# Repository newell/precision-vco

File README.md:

# Precision Voltage-Controlled Oscillator (VCO)

This circuit is a precision voltage-controlled oscillator (VCO), where the frequency of oscillation is determined by a control voltage. It consists of an integrator and a Schmitt trigger.

### Integrator
The first op-amp in the circuit acts as an integrator. The control voltage is divided using a voltage divider and applied to the positive input of the op-amp. The op-amp strives to keep its negative input at the same voltage level. This requires a current to flow through a resistor to maintain a specific voltage drop.

When a switch, such as a MOSFET, is on, the current from the resistor passes through the switch. Another resistor, connected in parallel with the switch, has a different resistance but the same voltage drop. As a result, it carries a different amount of current. This additional current either charges or discharges a capacitor, depending on the state of the switch. The integrator adjusts its output voltage to accommodate this current flow, resulting in a steadily rising or falling output voltage.

### Schmitt Trigger
The second op-amp in the circuit functions as a Schmitt trigger. It receives the output from the integrator as its input. The Schmitt trigger compares the input voltage with two threshold levels. When the input voltage rises above the upper threshold, the output switches to a high state. Conversely, when the input voltage falls below the lower threshold, the output switches to a low state. This behavior generates a square wave output.

The square wave output from the Schmitt trigger is connected to the switch (e.g., MOSFET) in the circuit. The switch controls the charging and discharging of the capacitor in the integrator circuit. As the square wave switches between its high and low states, it causes the integrator to adjust its output voltage accordingly, resulting in the generation of a triangle wave.

<!-- # aoe-precision-vco
Art of Electronics (AOE) Precision VCO

This circuit is based off of an AOE (Art of Electronics, 3rd Edition) circuit example found on page 267 (Figure 4.83). This circuit outputs triangle and square waves with frequencies equal to 200 * Vin Hz where Vin is from 0 to 2*Vref. In this circuit Vref is 5 V so we have a frequency range of 0 to 2 kHz -->

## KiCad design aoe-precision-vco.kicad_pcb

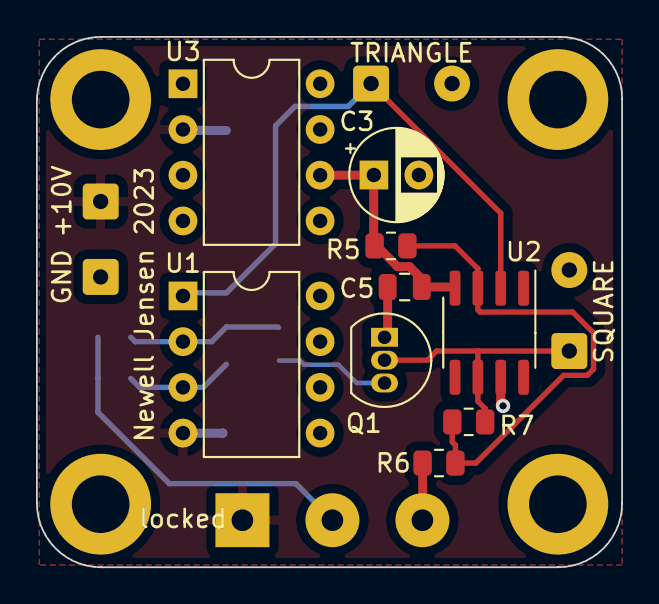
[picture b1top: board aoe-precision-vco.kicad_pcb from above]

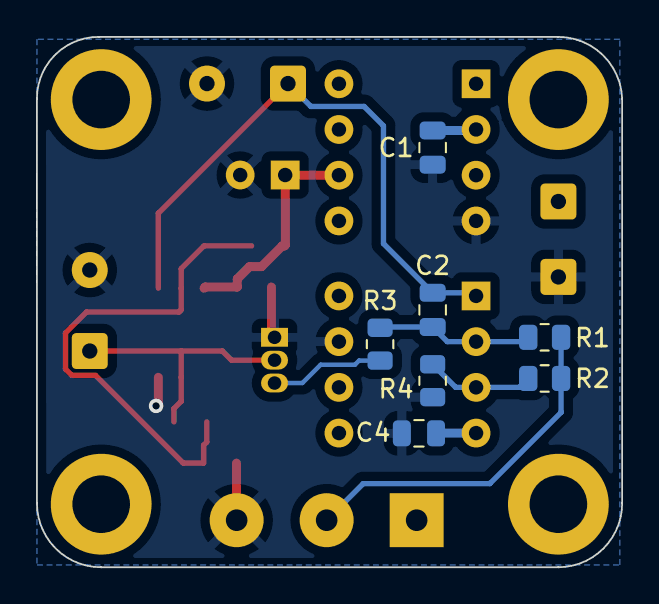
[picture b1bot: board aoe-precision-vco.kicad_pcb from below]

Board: 2 copper layers, 32.5 x 29.5 mm, 21 parts (7 on the bottom side), 10 nets.

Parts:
+10V: Conn_01x01; SolderWire-0.25sqmm_1x01_D0.65mm_OD2mm
C1, C2, C4, C5: 0.1uF; C_0805_2012Metric
C3: 4.7uF; CP_Radial_D5.0mm_P2.50mm
GND: Conn_01x01; SolderWire-0.25sqmm_1x01_D0.65mm_OD2mm
Q1: 2N7000; TO-92_Inline
R1: 7.5k; R_0805_2012Metric
R2, R4, R5, R6, R7: 10k; R_0805_2012Metric
R3: 3.74k; R_0805_2012Metric
SQUARE: Conn_Coaxial; SolderWire-0.25sqmm_1x02_P4.5mm_D0.65mm_OD2mm
TRIANGLE: Conn_Coaxial; SolderWire-0.25sqmm_1x02_P4.5mm_D0.65mm_OD2mm
U1: LT1077A; DIP-8_W7.62mm
U2: TLV3501; SOIC-8_3.9x4.9mm_P1.27mm
U3: LT1027DCN8-5; DIP-8_W7.62mm
locked: 10k; RV1_1

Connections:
+10V: +10V.1, C1.1, C4.2, U1.4 (V-), U3.2 (VIN), locked.1
GNDREF: C1.2, C3.2, C4.1, C5.1, GND.1, Q1.1 (S), R4.1, R6.2, SQUARE.2 (Ext), TRIANGLE.2 (Ext), U1.7 (V+), U2.7 (V+), U3.4 (GND), locked.3
unnamed: C2.1, R1.2, R3.2, U1.2 (-)
unnamed: C2.2, TRIANGLE.1 (In), U1.1, U2.2 (-)
unnamed: C3.1, C5.2, R5.1, U2.4 (V-), U3.6 (VOUT)
unnamed: Q1.2 (G), R7.2, SQUARE.1 (In), U2.6
unnamed: Q1.3 (D), R3.1
unnamed: R1.1, R2.1, locked.2
unnamed: R2.2, R4.2, U1.3 (+)
unnamed: R5.2, R6.1, R7.1, U2.3 (+)

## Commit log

2023-06-27 Add datasheets
2023-06-27 Add schematic
2023-06-27 Add pcb
